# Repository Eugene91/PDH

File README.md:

# Simple circuit for Pound-Drever-Hall stabilization
The circuit performs heterodyne detection of subcarrier phase from a photodetector 
by mixing it with local oscillator radio-frequency (RF) mixer. 

The circuit has two SMA inputs J1 and J2 for the phased-locked and signal  local oscillator, respectively. 
The scheme of the circuit is depicted below:

- Input signals from J1 and J2 are mixed in RF mixer Minicircuit ADE-1+. 
Prior to coming to mixer the signal from J2 is amplified by Minicircuit MAN1LN.
- The output from the RF mixer is low passed through an active filter based on OPA1604
with 4.5 KHz bandwidth and DC gain of 4.
- The low passed signal is inverted and amplified by inverting amplifier with variable DC gain up to 10 on OPA1604.
- The signal is summed with variable offset and is routed on 50 Ohm load through.

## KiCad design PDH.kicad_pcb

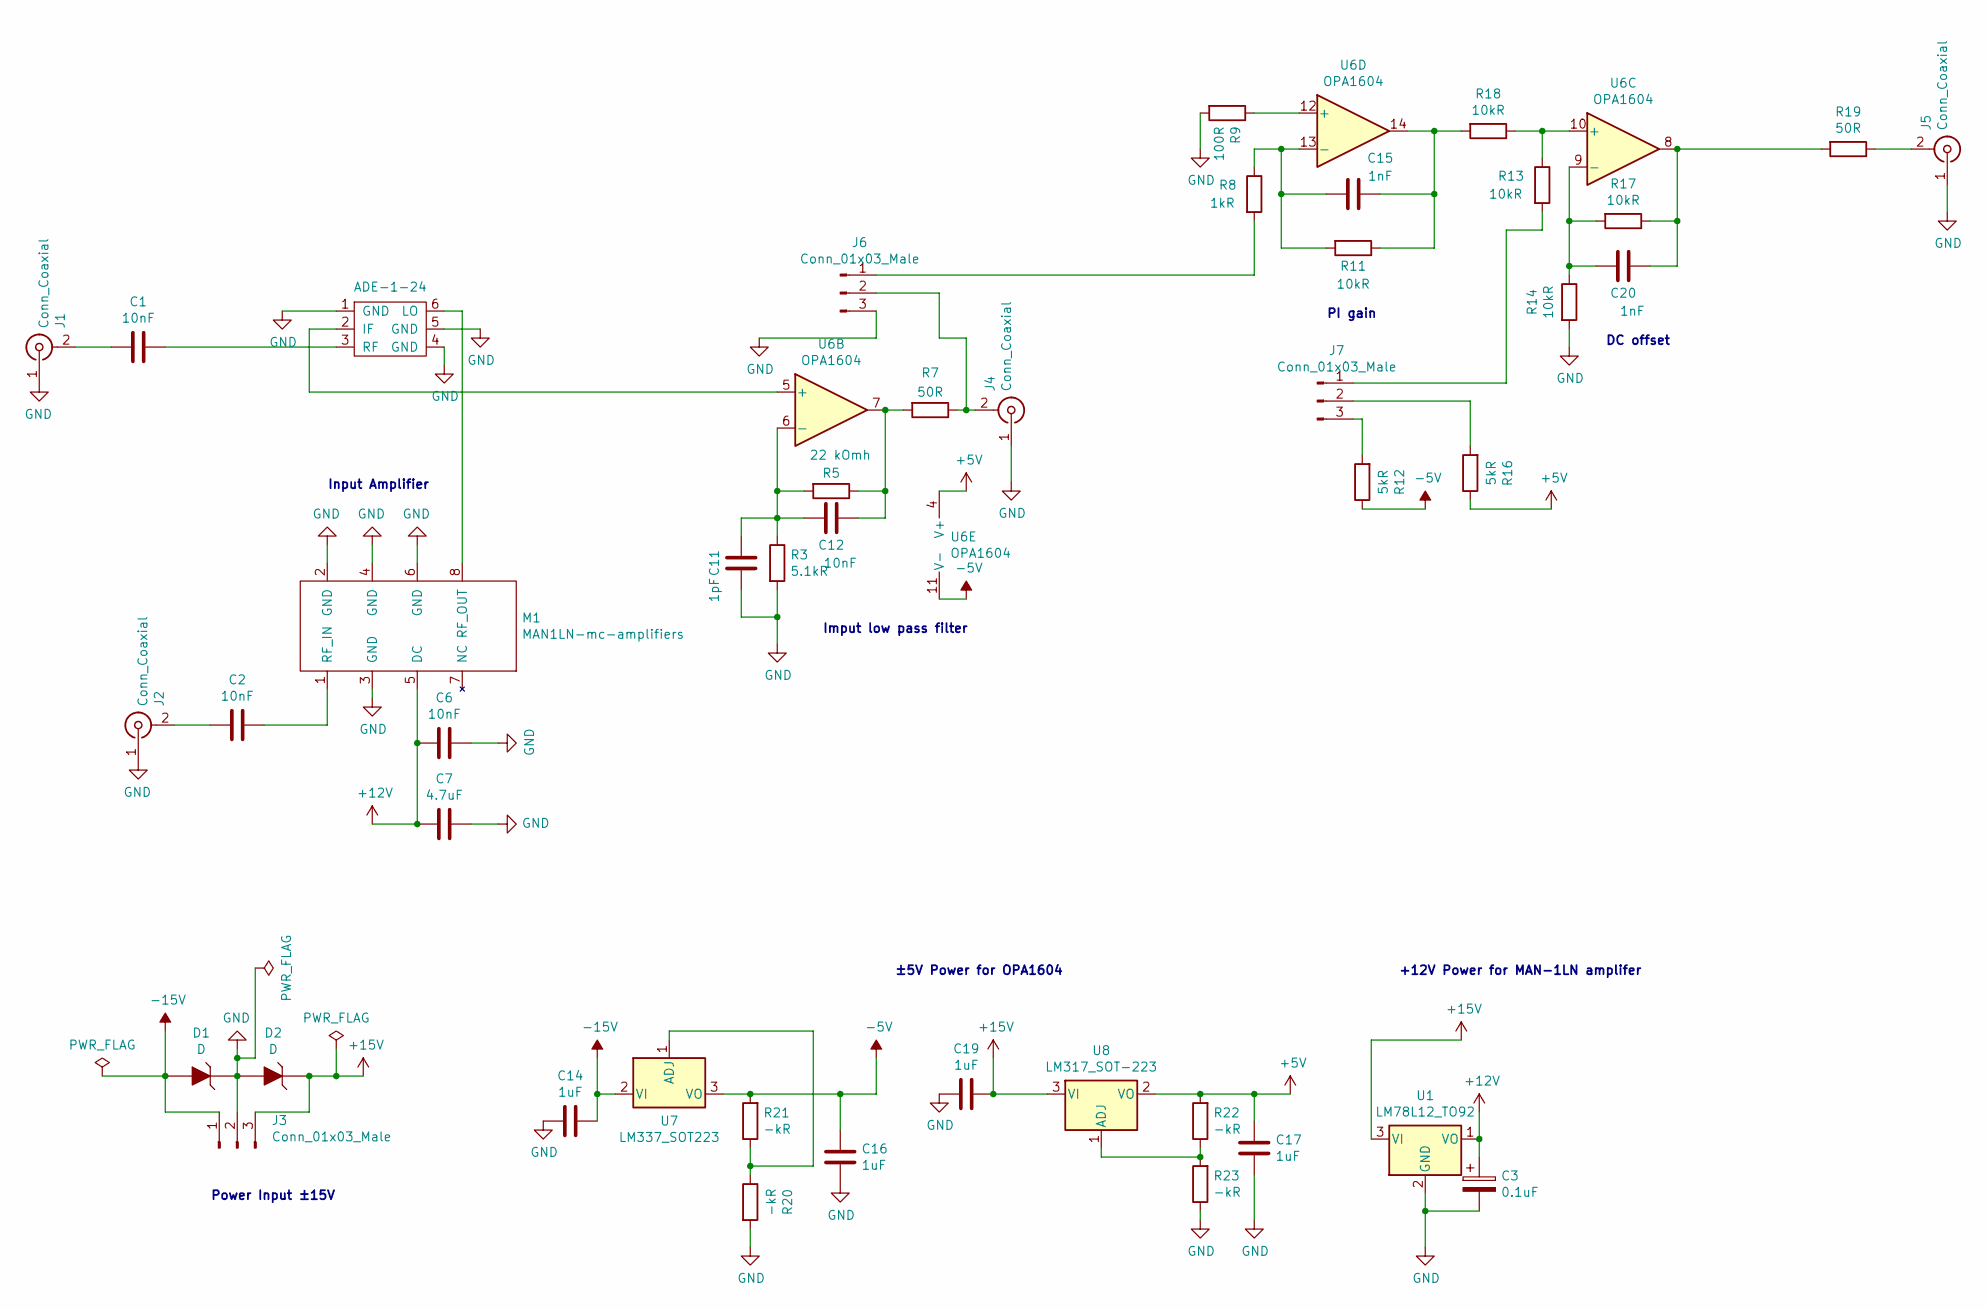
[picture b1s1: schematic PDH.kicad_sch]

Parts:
C1, C2, C6: 10nF; C_1206
C3: 0.1uF; CP_Radial_D5.0mm_P2.00mm
C7: 4.7uF; C_1206
C11: 1pF; C_0603
C12: 10nF; C_0603
C14, C19: 1uF; 1206
C15: 1nF; C_1206
C16, C17: 1uF; C_0603
C20: 1nF; 0603
D1, D2: D; Photodiode_1206
J1, J2, J4, J5: Conn_Coaxial; RF_SMA_Vertical_5-1814832-1
J3, J6, J7: Conn_01x03_Male; PinHeader_1x3_P2.54_Drill1.1mm
M1: MAN1LN-mc-amplifiers; A05
R3: 5.1kR; R_1206
R5: 22 kOmh; R_1206
R7: 50R; R_Axial_DIN0207_L6.3mm_D2.5mm_P7.62mm_Horizontal
R8: 1kR; R_1206
R9: 100R; R_1206
R11, R14, R17, R18: 10kR; R_1206
R12, R16: 5kR; R_Axial_DIN0207_L6.3mm_D2.5mm_P7.62mm_Horizontal
R13: 10kR; R_Axial_DIN0207_L6.3mm_D2.5mm_P7.62mm_Horizontal
R19: 50R; R_1206
R20, R21, R22, R23: -kR; R_1206
U1: LM78L12_TO92; TO-92-3
U6: OPA1604; TSSOP-14_4.4x5mm_P0.65mm
U7: LM337_SOT223; SOT-223
U8: LM317_SOT-223; SOT-223

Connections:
+5V: C17.1, R16.1, R22.2, U6.4 (V+), U8.2 (VO), U8.4
+12V: C3.1, C6.2, C7.2, M1.5 (DC), U1.1 (VO)
+15V: C19.1, D2.K, J3.3, U1.3 (VI), U8.3 (VI)
-5V: C16.1, R12.1, R21.2, U6.11 (V-), U7.3 (VO)
-15V: C14.1, D1.A, J3.1, U7.2 (VI), U7.4
GND: C3.2, C6.1, C7.1, C11.1, C14.2, C16.2, C17.2, C19.2, D1.K, D2.A, J1.1 (In), J2.1 (In), J3.2, J4.1 (In), J5.1 (In), J6.3, M1.2 (GND), M1.3 (GND), M1.4 (GND), M1.6 (GND), R3.2, R9.2, R14.2, R20.2, R23.1, U1.2 (GND); also elsewhere on the board
unnamed 6: U6.5 (+); also elsewhere on the board
unnamed 7: C1.2; also elsewhere on the board
unnamed 8: M1.8 (RF_OUT); also elsewhere on the board
unnamed: C1.1, J1.2 (Ext)
unnamed: C2.1, J2.2 (Ext)
unnamed: C2.2, M1.1 (RF_IN)
unnamed: C11.2, C12.2, R3.1, R5.2, U6.6 (-)
unnamed: C12.1, R5.1, R7.2, U6.7
unnamed: C15.1, R11.1, R18.2, U6.14
unnamed: C15.2, R8.1, R11.2, U6.13 (-)
unnamed: C20.1, R17.1, R19.2, U6.8
unnamed: C20.2, R14.1, R17.2, U6.9 (-)
unnamed: J4.2 (Ext), J6.2, R7.1
unnamed: J5.2 (Ext), R19.1
unnamed: J6.1, R8.2
unnamed: J7.1, R13.2
unnamed: J7.2, R16.2
unnamed: J7.3, R12.2
unnamed: R9.1, U6.12 (+)
unnamed: R13.1, R18.1, U6.10 (+)
unnamed: R20.1, R21.1, U7.1 (ADJ)
unnamed: R22.1, R23.2, U8.1 (ADJ)

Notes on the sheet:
PI gain
Imput low pass filter
±5V Power for OPA1604
+12V Power for MAN-1LN amplifer
Power Input ±15V
Input Amplifier
DC offset

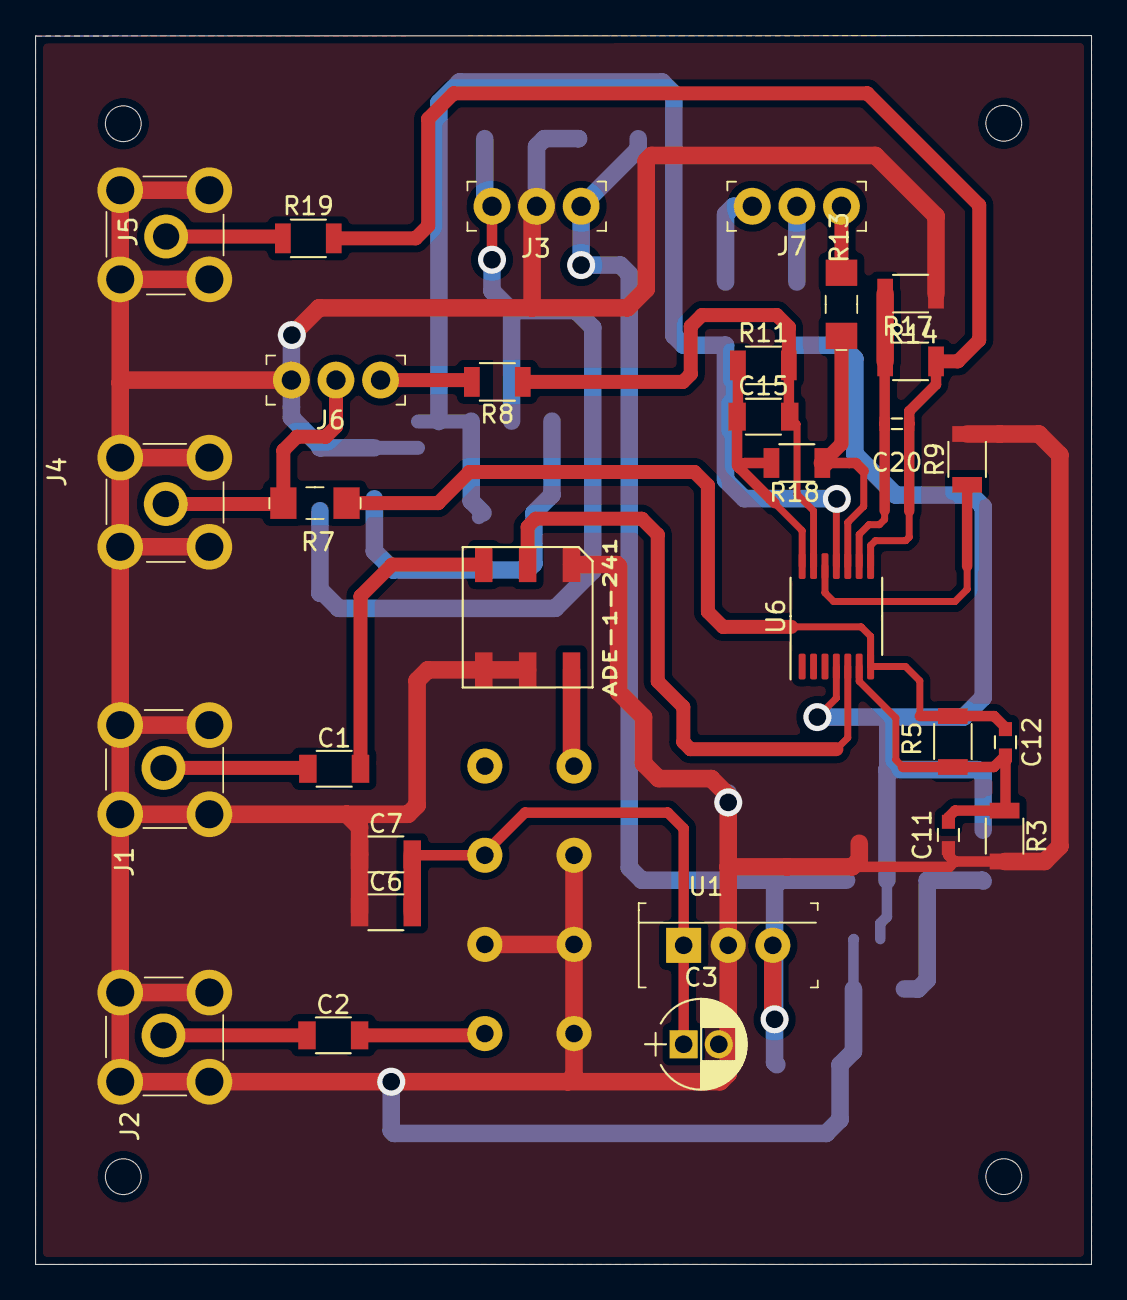
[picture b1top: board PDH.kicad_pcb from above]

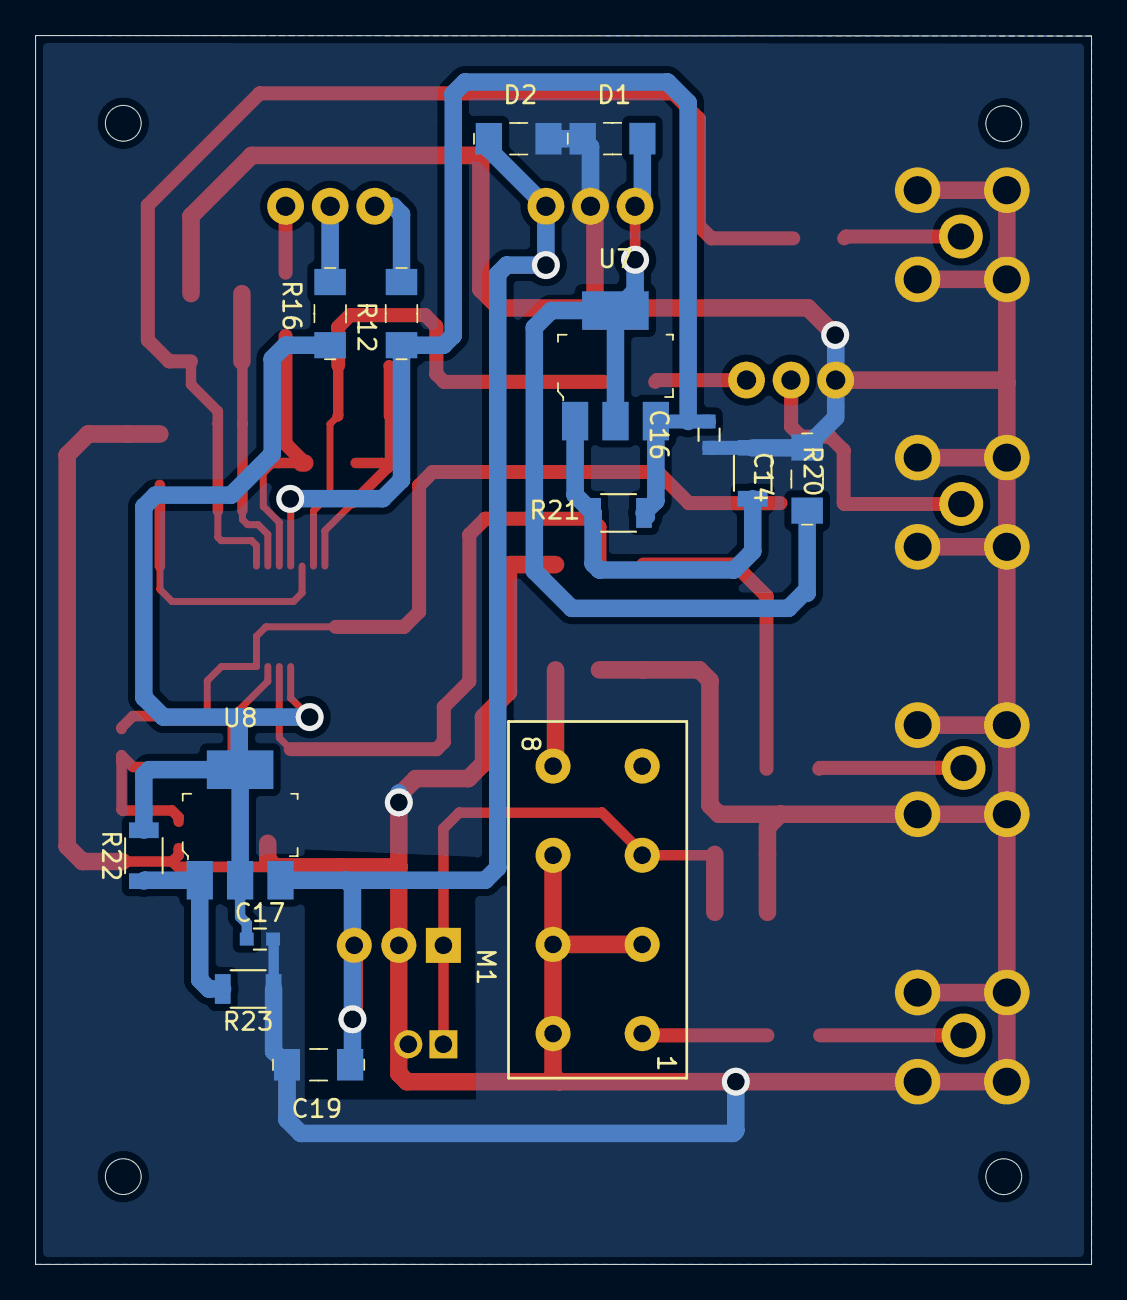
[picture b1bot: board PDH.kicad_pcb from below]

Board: 2 copper layers, 60.2 x 70.0 mm, 45 parts (15 on the bottom side), 28 nets.

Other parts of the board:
ADE-1-241: ADE-1-24

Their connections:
GND: ADE-1-241.1, ADE-1-241.4, ADE-1-241.5; also elsewhere on the board
unnamed 6: ADE-1-241.2; also elsewhere on the board
unnamed 7: ADE-1-241.3; also elsewhere on the board
unnamed 8: ADE-1-241.6; also elsewhere on the board

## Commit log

2023-01-23 Minor Update
